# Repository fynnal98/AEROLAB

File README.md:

# AEROLAB – Repository Collection

This repository is used to collect and organize my other projects.  
All projects are included here as git submodules.

Clone with: 
git clone --recurse-submodules git@github.com:fynnal98/AEROLAB.git

for add submodule later: 
git submodule update --init --recursive

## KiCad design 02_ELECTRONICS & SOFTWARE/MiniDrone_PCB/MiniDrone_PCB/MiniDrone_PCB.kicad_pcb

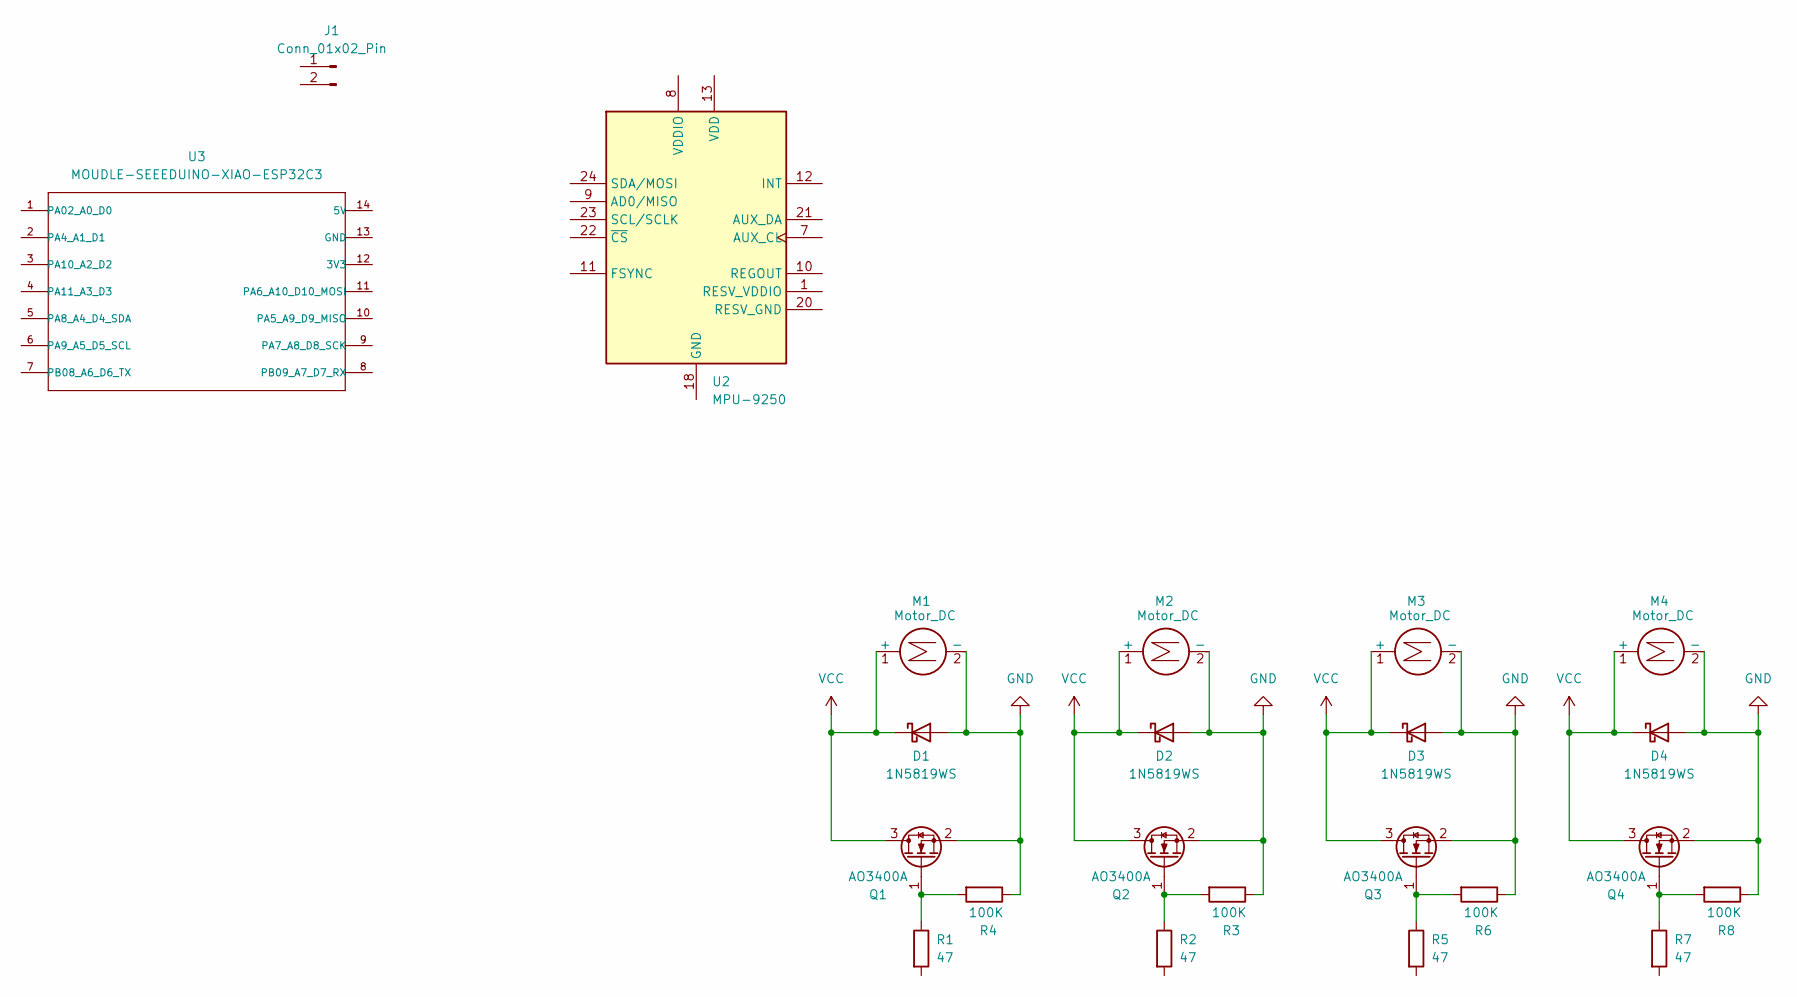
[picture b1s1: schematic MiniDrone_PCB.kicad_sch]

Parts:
D1, D2, D3, D4: 1N5819WS; D_SOD-323
J1: Conn_01x02_Pin; PinHeader_1x02_P2.54mm_Vertical
M1, M2, M3, M4: Motor_DC; TestPoint_2Pads_Pitch2.54mm_Drill0.8mm
Q1, Q2, Q3, Q4: AO3400A; SOT-23
R1, R2, R5, R7: 47; R_0805_2012Metric
R3, R4, R6, R8: 100K; R_0805_2012Metric
U2: MPU-9250; InvenSense_QFN-24_3x3mm_P0.4mm
U3: MOUDLE-SEEEDUINO-XIAO-ESP32C3; MCU_Seeed_ESP32C3

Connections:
GND: D1.2 (A), D2.2 (A), D3.2 (A), D4.2 (A), M1.2 (-), M2.2 (-), M3.2 (-), M4.2 (-), Q1.2 (S), Q2.2 (S), Q3.2 (S), Q4.2 (S), R3.1, R4.1, R6.1, R8.1
unnamed: Q1.1 (G), R1.1, R4.2
unnamed: Q2.1 (G), R2.1, R3.2
unnamed: Q3.1 (G), R5.1, R6.2
unnamed: Q4.1 (G), R7.1, R8.2
VCC: D1.1 (K), D2.1 (K), D3.1 (K), D4.1 (K), M1.1 (+), M2.1 (+), M3.1 (+), M4.1 (+), Q1.3 (D), Q2.3 (D), Q3.3 (D), Q4.3 (D)

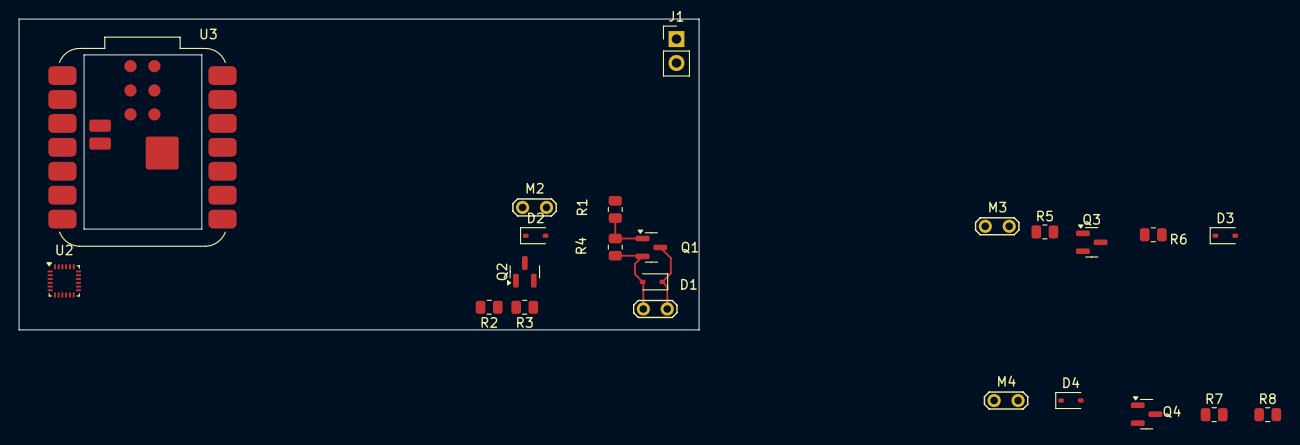
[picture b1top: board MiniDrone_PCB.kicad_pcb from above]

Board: 2 copper layers, 72.2 x 33.0 mm, 23 parts (0 on the bottom side), 6 nets.

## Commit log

2025-08-20 Ordnerstruktur mit README-Dateien angelegt
2025-08-20 MINI DRONE
2025-08-21 Gyro, ACC, PID, Failsafe
2025-08-21 Name
2025-08-28 airbert CAD
2025-09-01 add Hubert as submodule
2025-09-01 structure
2025-09-01 Remove submodule ESP32-Drone
2025-09-01 Add submodule ESP32-Drone
2025-09-01 Add submodule ESP32-Drone clean
2025-09-01 Fix submodule ESP32-Drone (remove stale entry, add clean)
